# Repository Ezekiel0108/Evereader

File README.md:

# Evereader
## What is it?
It is an esp32-s3 module based e-reader with dual screens that should be easy enough for anyone to build and customize.
### Why does this project exist?
There are two main reasons:
1. I really wanted to make a project bigger than what i had done until now, i want to give back at least in some way to the foss community;
2. I have been getting a lot into reading lately and i really wanted an e-reader, but none of them actually felt right for me, either they where too big to put in a pocket or the smaller ones just didn't fit enough content for my taste.
### Why two screens?
1. Why not?
2. I really wanted to keep the form factor pocketable without sacrificing text on screen, so i put two!
#### State of developement
I am currently just ending the breadboard circuit, after that i want to start making the PCB and develop the firmware.
#### TO-DO list
- [x] Finish up the breadboard circuit.
- [ ] Finish up the PCB kicad project.
- [ ] Finish up the software.
- [ ] Refine what i can.
- [ ] Add images to the readme.

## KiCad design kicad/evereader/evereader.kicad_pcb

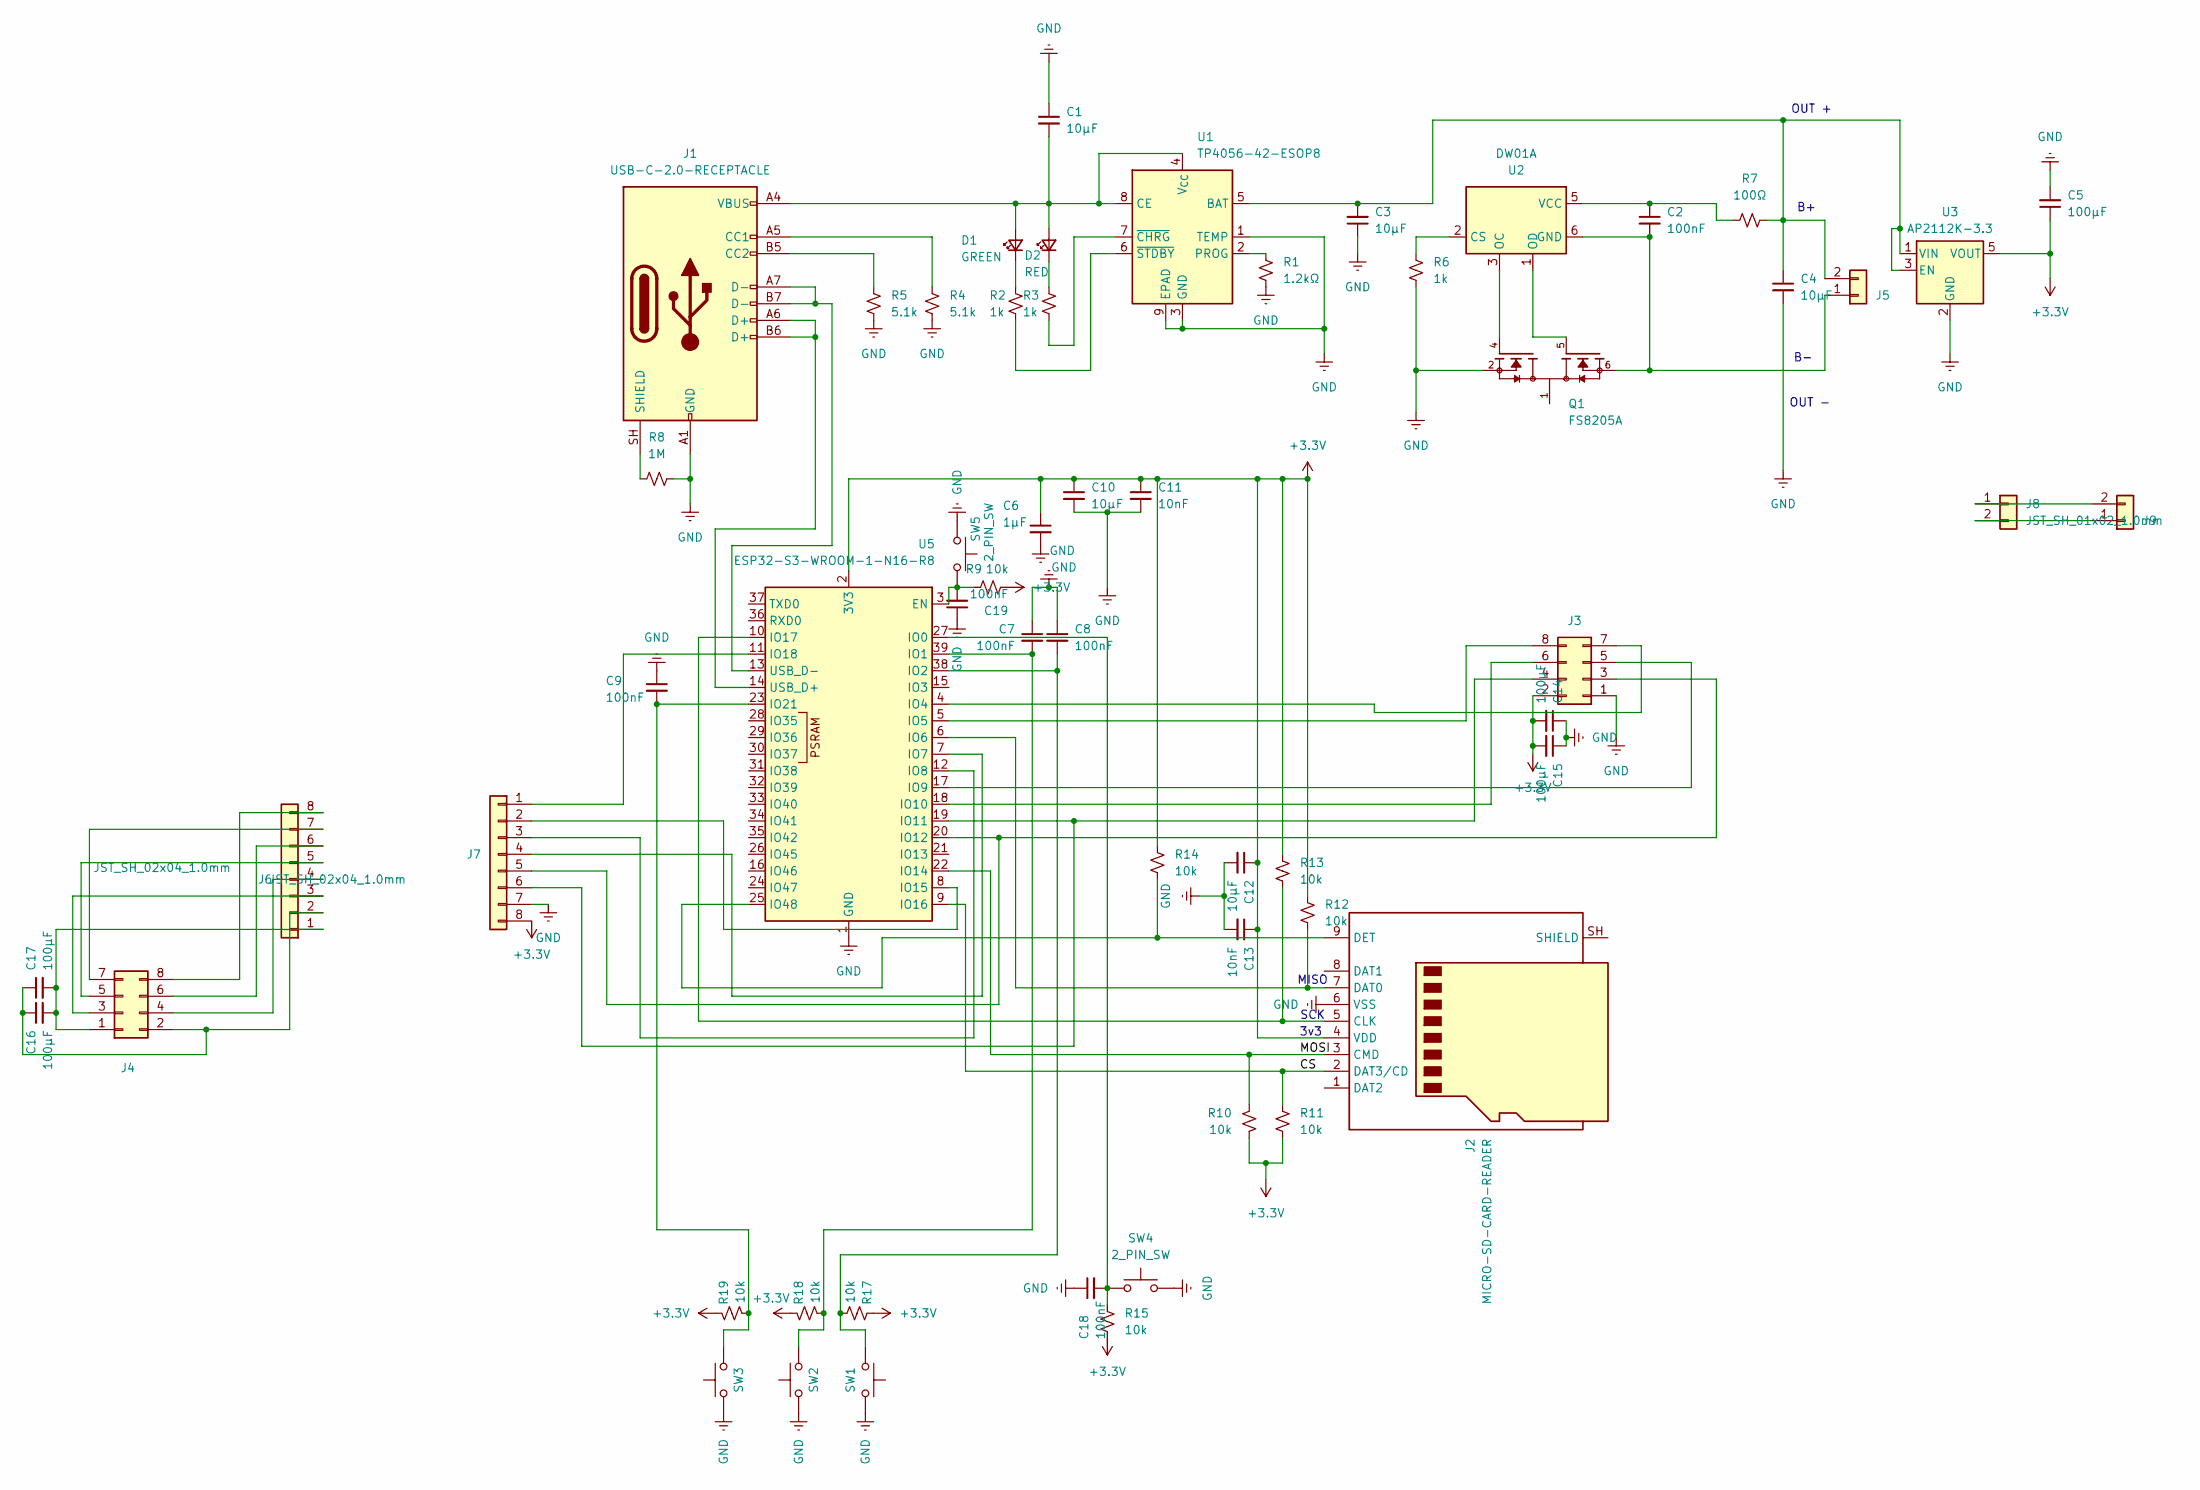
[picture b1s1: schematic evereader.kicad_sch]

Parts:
C1, C3, C4, C10, C12: 10μF; C_0805_2012Metric; JLCPCB C15850
C2, C7, C8, C9, C18, C19: 100nF; C_0805_2012Metric
C5: 100μF; C_1206_3216Metric; JLCPCB C28323
C6: 1μF; C_0805_2012Metric; JLCPCB C28323
C11, C13: 10nF; C_0805_2012Metric
C14, C15, C16, C17: 100μF; C_1206_3216Metric
D1: GREEN; LED_0805_2012Metric
D2: RED; LED_0805_2012Metric
J1: USB-C-2.0-RECEPTACLE; USB_C_Receptacle_HRO_TYPE-C-31-M-12; JLCPCB C165948
J2: MICRO-SD-CARD-READER; TF-SMD_TF-115-BCP9; JLCPCB C720505
J3, J4: PinHeader_2x04_P2.54mm_Vertical
J5, J8: JST_SH_01x02_1.0mm; CONN-SMD_2P-P1.00_SM02B-SRSS-TB-LF-SN; JLCPCB C160402
J6, J7: JST_SH_02x04_1.0mm; CONN-TH_SM08B-SRSS-TB-LF-SN; JLCPCB C160407
J9: PinHeader_1x02_P2.54mm_Vertical
Q1: FS8205A; TSSOP-8_L4.4-W3.0-P0.65-LS6.4-BL; PARTREV 1.7; JLCPCB C7525054
R1: 1.2kΩ; R_0805_2012Metric
R2, R3, R6: 1k; R_0805_2012Metric
R4, R5: 5.1k; R_0805_2012Metric
R7: 100Ω; R_0805_2012Metric
R8: 1M; R_0805_2012Metric
R9, R10, R11, R12, R13, R14, R15, R17, R18, R19: 10k; R_0805_2012Metric
SW1, SW2, SW3: SW_Push; SW_SPST_PTS645Sx43SMTR92
SW4, SW5: 2_PIN_SW; SW_Push_SPST_NO_Alps_SKRK
U1: TP4056-42-ESOP8; SOIC-8-1EP_3.9x4.9mm_P1.27mm_EP2.41x3.3mm_ThermalVias; JLCPCB C139797
U2: DW01A; SOT-23-6
U3: AP2112K-3.3; SOT-23-5
U5: ESP32-S3-WROOM-1-N16-R8; ESP32-S3-WROOM-1

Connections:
+3.3V: C5.1, C6.1, C10.1, C11.1, C12.1, C13.1, C14.2, C15.2, J2.4 (VDD), J3.2, J7.8, R9.2, R10.2, R11.2, R12.1, R13.1, R14.1, R15.2, R17.1, R18.1, R19.1, U3.5 (VOUT), U5.2 (3V3)
/CS: J2.2 (DAT3/CD), R11.1, U5.9 (IO16)
/MOSI: J2.3 (CMD), R10.1, U5.22 (IO14)
GND: C1.1, C3.1, C4.2, C5.2, C6.2, C7.1, C8.1, C9.1, C10.2, C11.2, C12.2, C13.2, C14.1, C15.1, C18.1, C19.1, J1.A1 (GND), J1.A12 (GND), J1.B1 (GND), J1.B12 (GND), J2.6 (VSS), J3.1, J7.7, Q1.2, Q1.3, R1.2, R4.2, R5.2, R6.2, R8.2, SW1.2, SW2.2, SW3.2, SW4.2, SW5.1, U1.1 (TEMP), U1.3 (GND), U1.9 (EPAD), U3.2 (GND), U5.1 (GND), U5.40 (GND), U5.41 (GND)
unnamed: C1.2, D1.2 (A), D2.2 (A), J1.A4 (VBUS), J1.A9 (VBUS), J1.B4 (VBUS), J1.B9 (VBUS), U1.4 (V_{CC}), U1.8 (CE)
unnamed: D1.1 (K), R2.1
unnamed: D2.1 (K), R3.1
unnamed: J1.A5 (CC1), R4.1
unnamed: J1.B5 (CC2), R5.1
unnamed: J1.SH (SHIELD), R8.1
unnamed: J2.5 (CLK), R13.2, U5.10 (IO17)
unnamed: J2.7 (DAT0), R12.2, U5.6 (IO6)
unnamed: J2.9 (DET), R14.2, U5.25 (IO48)
unnamed: J3.3, J7.5, U5.20 (IO12)
unnamed: J3.4, J7.6, U5.19 (IO11)
unnamed: J3.5, U5.17 (IO9)
unnamed: J3.6, U5.18 (IO10)
unnamed: J3.7, U5.4 (IO4)
unnamed: J3.8, U5.5 (IO5)
unnamed: C16.2, C17.2, J4.1, J6.1
unnamed: C16.1, C17.1, J4.2, J6.2
unnamed: J4.3, J6.3
unnamed: J4.4, J6.4
unnamed: J4.5, J6.5
unnamed: J4.6, J6.6
unnamed: J4.7, J6.7
unnamed: J4.8, J6.8
unnamed: C2.2, J5.1, Q1.6, Q1.7, U2.6 (GND)
unnamed: C3.2, C4.1, J5.2, R7.2, U1.5 (BAT), U3.1 (VIN), U3.3 (EN)
unnamed: J7.1, U5.11 (IO18)
unnamed: J7.2, U5.8 (IO15)
unnamed: J7.3, U5.12 (IO8)
unnamed: J7.4, U5.7 (IO7)
unnamed: J8.1, J9.2
unnamed: J8.2, J9.1
unnamed: Q1.1, Q1.8
unnamed: R1.1, U1.2 (PROG)
unnamed: R3.2, U1.7 (~CHRG)
unnamed: R2.2, U1.6 (~STDBY)
unnamed: R6.1, U2.2 (CS)
unnamed: Q1.4, U2.3 (OC)
unnamed: Q1.5, U2.1 (OD)
unnamed: C2.1, R7.1, U2.5 (VCC)
unnamed: C19.2, R9.1, SW5.2, U5.3 (EN)
unnamed: C18.2, R15.1, SW4.1, U5.27 (IO0)
unnamed: C7.2, R18.2, SW2.1, U5.39 (IO1)
unnamed: C8.2, R17.2, SW1.1, U5.38 (IO2)
unnamed: C9.2, R19.2, SW3.1, U5.23 (IO21)
unnamed: J1.A6 (D+), J1.B6 (D+), U5.14 (USB_D+)
unnamed: J1.A7 (D-), J1.B7 (D-), U5.13 (USB_D-)

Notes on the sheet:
MISO
SCK
3v3
OUT +
OUT -

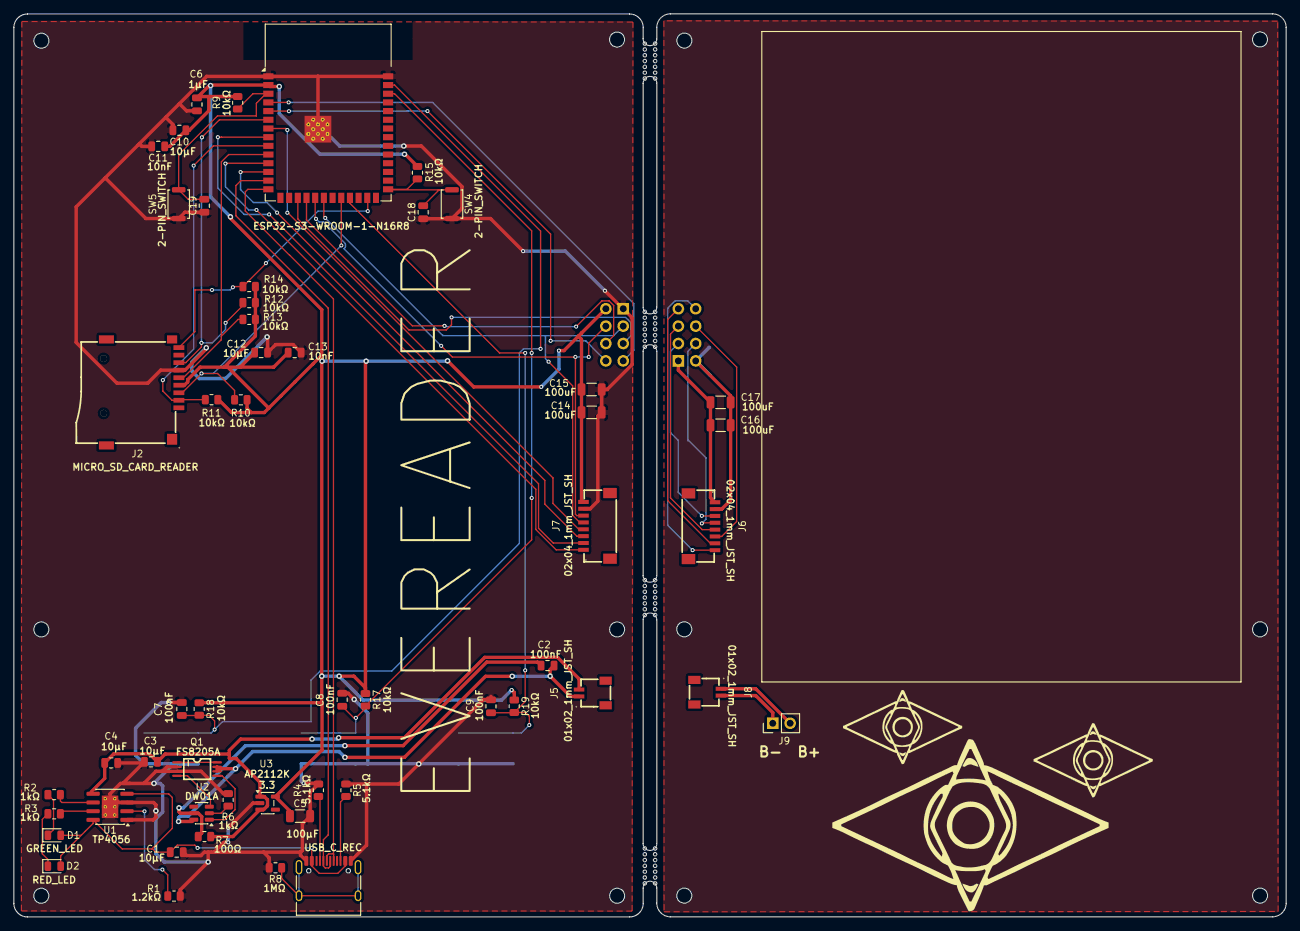
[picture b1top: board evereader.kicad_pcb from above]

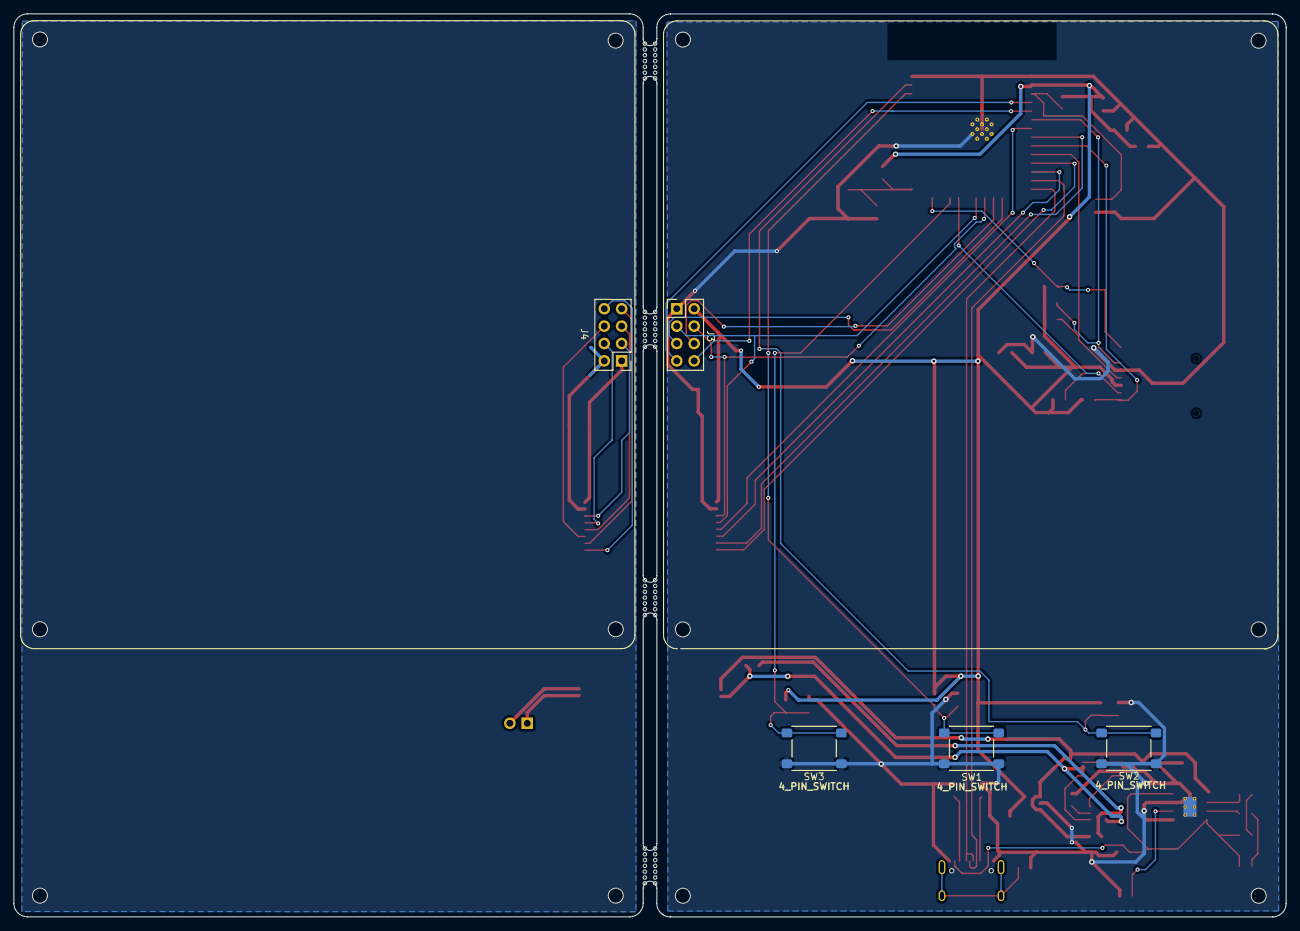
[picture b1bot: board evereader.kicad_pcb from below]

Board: 2 copper layers, 185.9 x 132.0 mm, 58 parts (5 on the bottom side), 50 nets.

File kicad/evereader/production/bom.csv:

Designator,Footprint,Quantity,Value,LCSC Part #
"C1, C10, C12, C3, C4",0805,5,C15850,
"C11, C13",0805,2,10nF,
"C14, C15, C16, C17",1206,4,100μF,
"C2, C7, C8, C9",0805,4,100nF,
"C5, C6",0805,2,C28323,
D1,0805,1,GREEN,
D2,0805,1,RED,
J1,USB_C_Receptacle_HRO_TYPE-C-31-M-12,1,C165948,
J2,TF-SMD_TF-115-BCP9,1,C720505,C720505
"J3, J4",PinHeader_2x04_P2.54mm_Vertical,2,~,
"J5, J8",JST_SH_SM02B-SRSS-TB_1x02-1MP_P1.00mm_Horizontal,2,C160402,
"J6, J7",JST_SH_SM08B-SRSS-TB_1x08-1MP_P1.00mm_Horizontal,2,C160407,
J9,PinHeader_1x02_P2.54mm_Vertical,1,~,
Q1,TSSOP-8_L4.4-W3.0-P0.65-LS6.4-BL,1,C7525054,C7525054
R1,0805,1,1.2kΩ,
"R10, R11, R12, R13, R14, R15, R17, R18, R19, R9",0805,10,10k,
"R2, R3, R6",0805,3,1k,
"R4, R5",0805,2,5.1k,
R7,0805,1,100Ω,
R8,0805,1,1M,
"SW1, SW2, SW3",SW_SPST_PTS645Sx43SMTR92,3,SW_Push,
"SW4, SW5",SW_Push_SPST_NO_Alps_SKRK,2,C139797,
U1,SOIC-8-1EP_3.9x4.9mm_P1.27mm_EP2.41x3.3mm_ThermalVias,1,TP4056-42-ESOP8,
U2,SOT-23-6,1,DW01A,
U3,SOT-23-5,1,AP2112K-3.3,
U5,ESP32-S3-WROOM-1,1,ESP32-S3-WROOM-1-N16-R8,

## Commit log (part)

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2026-06-08 Added license
2026-06-10 Added 0xProto font in include library (renamed to OxProto to avoid errors)
2026-06-10 Added simple backup file for testing out sd card
2026-06-10 Added logic for second screen and replaced old font with 0xProto_Regular
2026-06-10 Fixed up right screen lock and tidied up code a bit
2026-06-14 Fixed up some code stuff
2026-06-28 Gave SD a separate SPI bus!
